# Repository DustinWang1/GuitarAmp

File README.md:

# GuitarAmp
Project files for a guitar amp. Material and parts cost ~120. <br/>
Link to container CAD: https://cad.onshape.com/documents/430e134f113621e72c0b0a07/w/2a6cd6c6330c856296a7da6e/e/e5ffe4d51dda978353fd79e9?renderMode=0&uiState=6872a2335838dc772d2552cf<br/>
Front top and side walls are MDF. Base is hardwood. </br>

Speaker: Celestion Eight 15</br>
Op-Amps: TL072</br>
Transistor: TIP47</br>
All potentiometers are linear. Optionally, use logarithmic taper for gain knob.</br>

Use low-ESR ceramic capacitors for bypassing. Linear potentiometers were sourced from AmplifiedParts.com.</br>

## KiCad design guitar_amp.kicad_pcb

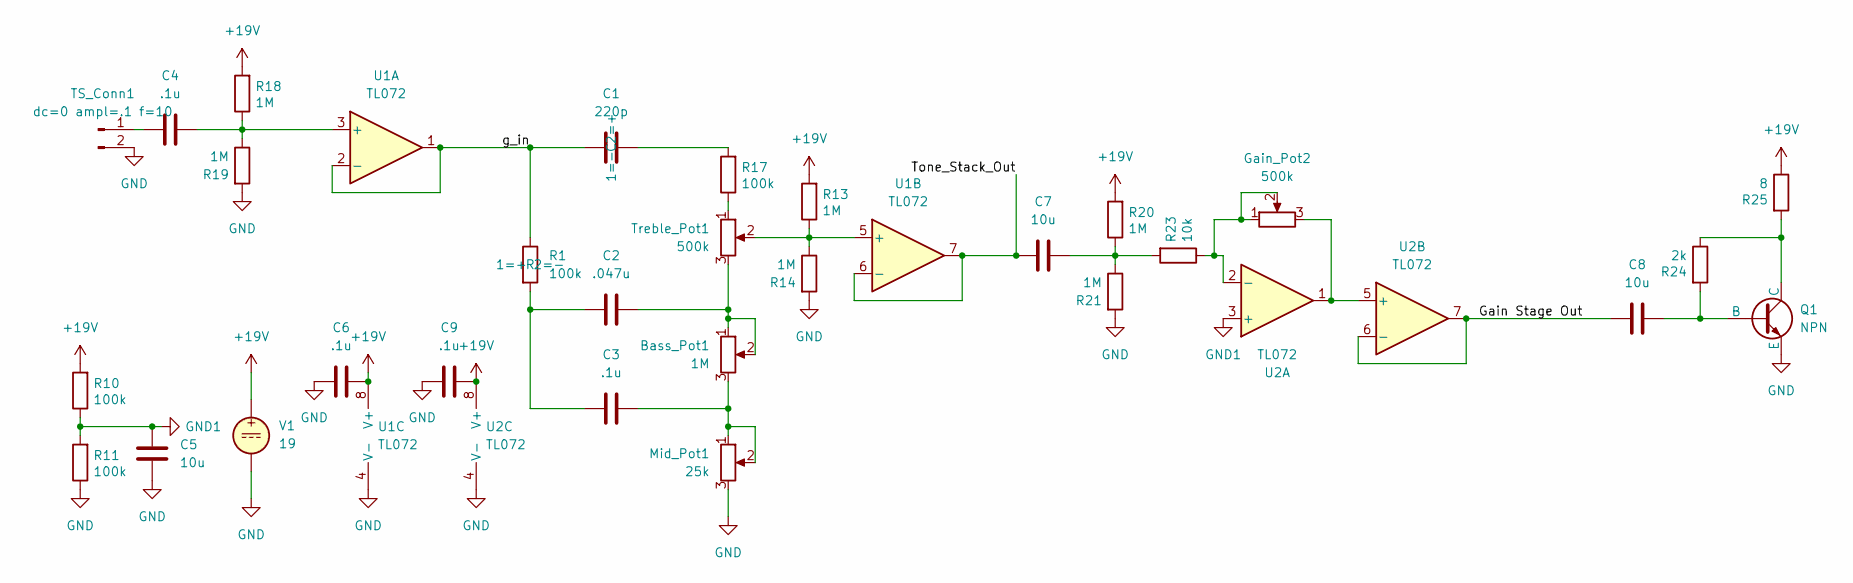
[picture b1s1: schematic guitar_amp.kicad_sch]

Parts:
Bass_Pot1: 1M; Screw_term_3_P5.00_1
C1: 220p; C_Disc_D8.0mm_W2.5mm_P5.00mm
C2: .047u; C_Rect_L16.5mm_W5.0mm_P15.00mm_MKT
C3, C4: .1u; C_Rect_L13.0mm_W5.0mm_P10.00mm_FKS3_FKP3_MKS4
C5, C7, C8: 10u; C_Axial_L12.0mm_D6.5mm_P20.00mm_Horizontal
C6, C9: .1u; C_Disc_D8.0mm_W2.5mm_P5.00mm
Gain_Pot2: 500k; Screw_term_3_P5.00_1
Mid_Pot1: 25k; Screw_term_3_P5.00_1
Q1: NPN; TO-220-3_Vertical
R1, R10, R11, R17: 100k; R_Axial_DIN0204_L3.6mm_D1.6mm_P7.62mm_Horizontal
R13, R14, R18, R19, R20, R21: 1M; R_Axial_DIN0204_L3.6mm_D1.6mm_P7.62mm_Horizontal
R23: 10k; R_Axial_DIN0204_L3.6mm_D1.6mm_P7.62mm_Horizontal
R24: 2k; R_Axial_DIN0204_L3.6mm_D1.6mm_P7.62mm_Horizontal
R25: 8; Screw_term_2_P5.00
TS_Conn1: dc=0 ampl=.1 f=10; Screw_term_2_P5.00
Treble_Pot1: 500k; Screw_term_3_P5.00_1
U1, U2: TL072; CERDIP-8_W7.62mm_SideBrazed_LongPads_Socket
V1: 19; Screw_term_2_P5.00

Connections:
+19V: C6.2, C9.2, R10.2, R13.2, R18.2, R20.2, R25.1, U1.8 (V+), U2.8 (V+), V1.1
/Gain Stage Out: C8.1, U2.6 (-), U2.7
/Tone_Stack_Out: C7.1, U1.6 (-), U1.7
/g_in: C1.1, R1.1, U1.1, U1.2 (-)
GND: C5.2, C6.1, C9.1, Mid_Pot1.3, Q1.3 (E), R11.1, R14.2, R19.2, R21.2, TS_Conn1.2, U1.4 (V-), U2.4 (V-), V1.2
GND1: C5.1, R10.1, R11.2, U2.3 (+)
unnamed: Bass_Pot1.1, Bass_Pot1.2, C2.2, Treble_Pot1.3
unnamed: Bass_Pot1.3, C3.2, Mid_Pot1.1, Mid_Pot1.2
unnamed: C1.2, R17.2
unnamed: C2.1, C3.1, R1.2
unnamed: C7.2, R20.1, R21.1, R23.2
unnamed: C8.2, Q1.1 (B), R24.2
unnamed: Q1.2 (C), R24.1, R25.2
unnamed: R17.1, Treble_Pot1.1
unnamed: C4.1, TS_Conn1.1
unnamed: C4.2, R18.1, R19.1, U1.3 (+)
unnamed: R13.1, R14.1, Treble_Pot1.2, U1.5 (+)
unnamed: Gain_Pot2.1, Gain_Pot2.2, R23.1, U2.2 (-)
unnamed: Gain_Pot2.3, U2.1, U2.5 (+)

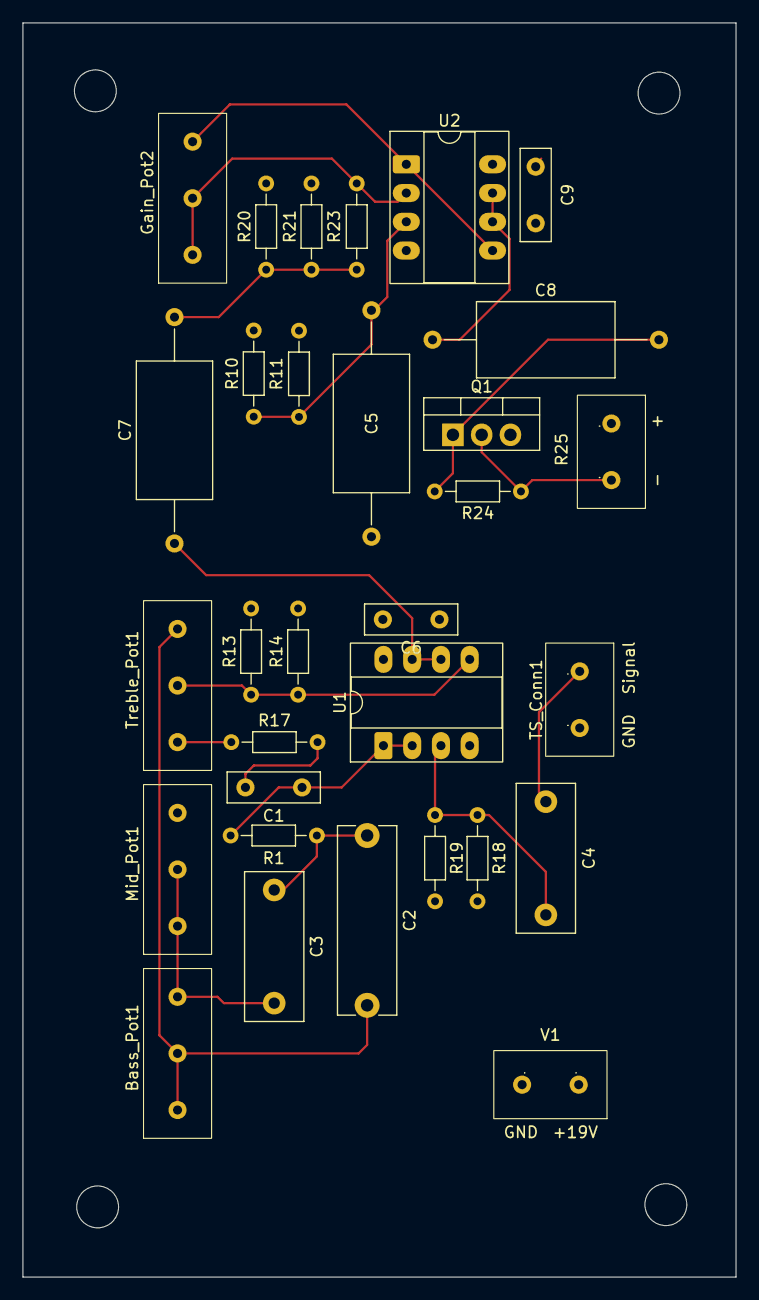
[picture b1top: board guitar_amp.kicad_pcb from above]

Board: 4 copper layers, 63.0 x 110.8 mm, 31 parts (0 on the bottom side), 19 nets.
